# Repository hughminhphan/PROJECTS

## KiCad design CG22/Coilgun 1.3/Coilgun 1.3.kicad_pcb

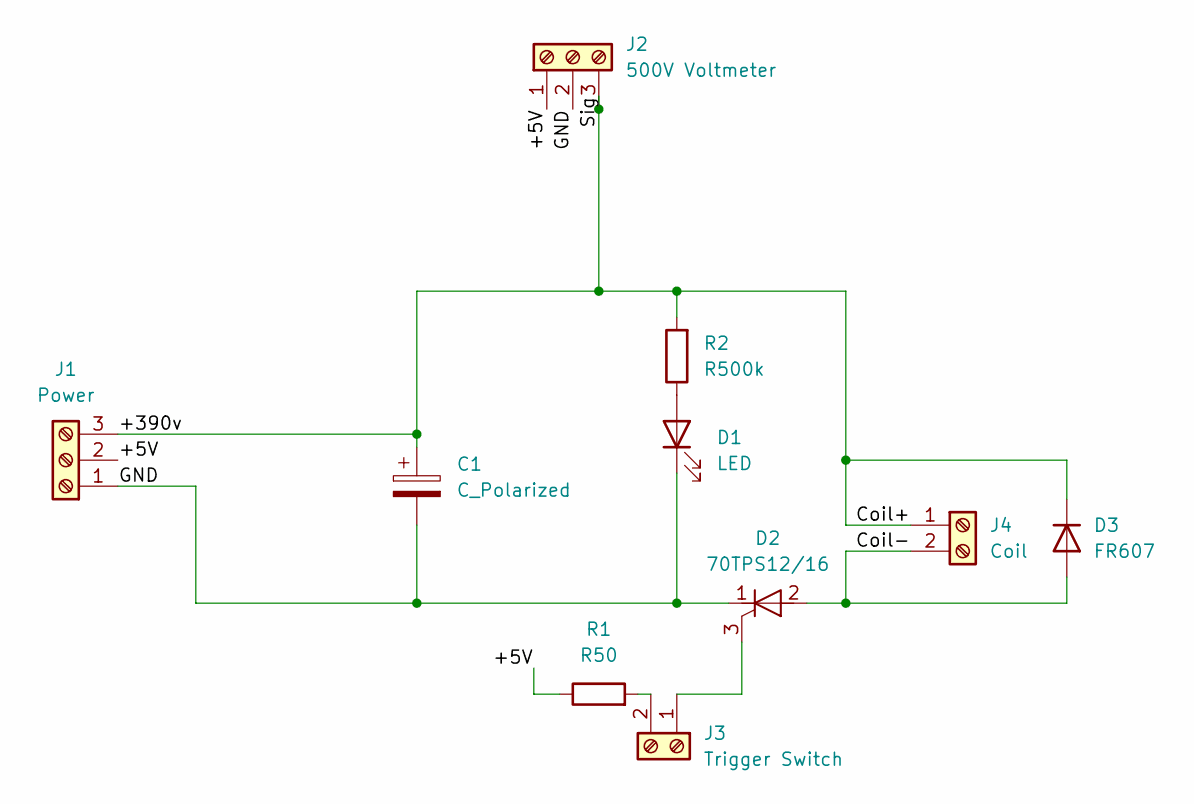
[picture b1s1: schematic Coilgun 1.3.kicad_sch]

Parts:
C1: C_Polarized
D1: LED; LED_D5.0mm
D2: 70TPS12/16; TO-247-3_Vertical
D3: FR607; D_DO-27_P15.24mm_Horizontal
J1: Power; TerminalBlock_bornier-3_P5.08mm
J2: 500V Voltmeter; TerminalBlock_bornier-3_P5.08mm
J3: Trigger Switch; TerminalBlock_bornier-2_P5.08mm
J4: Coil; TerminalBlock_bornier-2_P5.08mm
R1: R50; R_Axial_DIN0309_L9.0mm_D3.2mm_P12.70mm_Horizontal
R2: R500k; R_Axial_DIN0309_L9.0mm_D3.2mm_P12.70mm_Horizontal

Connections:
/+5V: J1.2, J2.1, R1.1
/+390v: C1.1, D3.1 (K), J1.3, J2.3, J4.1, R2.2
/Coil-: D2.2 (A), D3.2 (A), J4.2
/GND: C1.2, D1.1 (K), D2.1 (K), J1.1, J2.2
unnamed: D1.2 (A), R2.1
unnamed: D2.3 (G), J3.1
unnamed: J3.2, R1.2

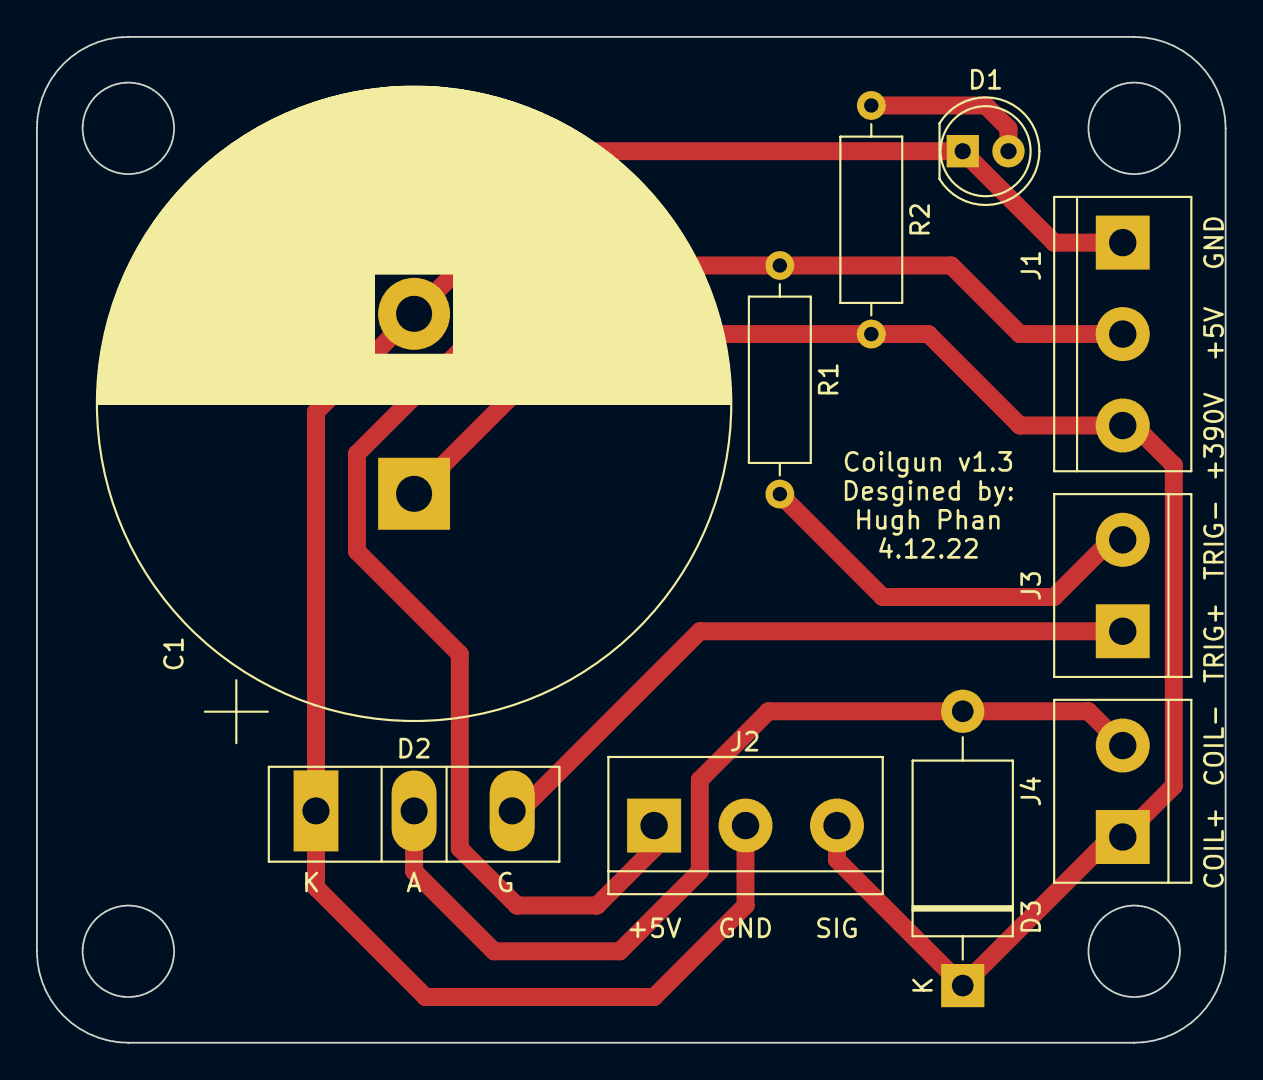
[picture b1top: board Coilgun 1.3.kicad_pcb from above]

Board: 2 copper layers, 66.0 x 55.9 mm, 10 parts (0 on the bottom side), 7 nets.

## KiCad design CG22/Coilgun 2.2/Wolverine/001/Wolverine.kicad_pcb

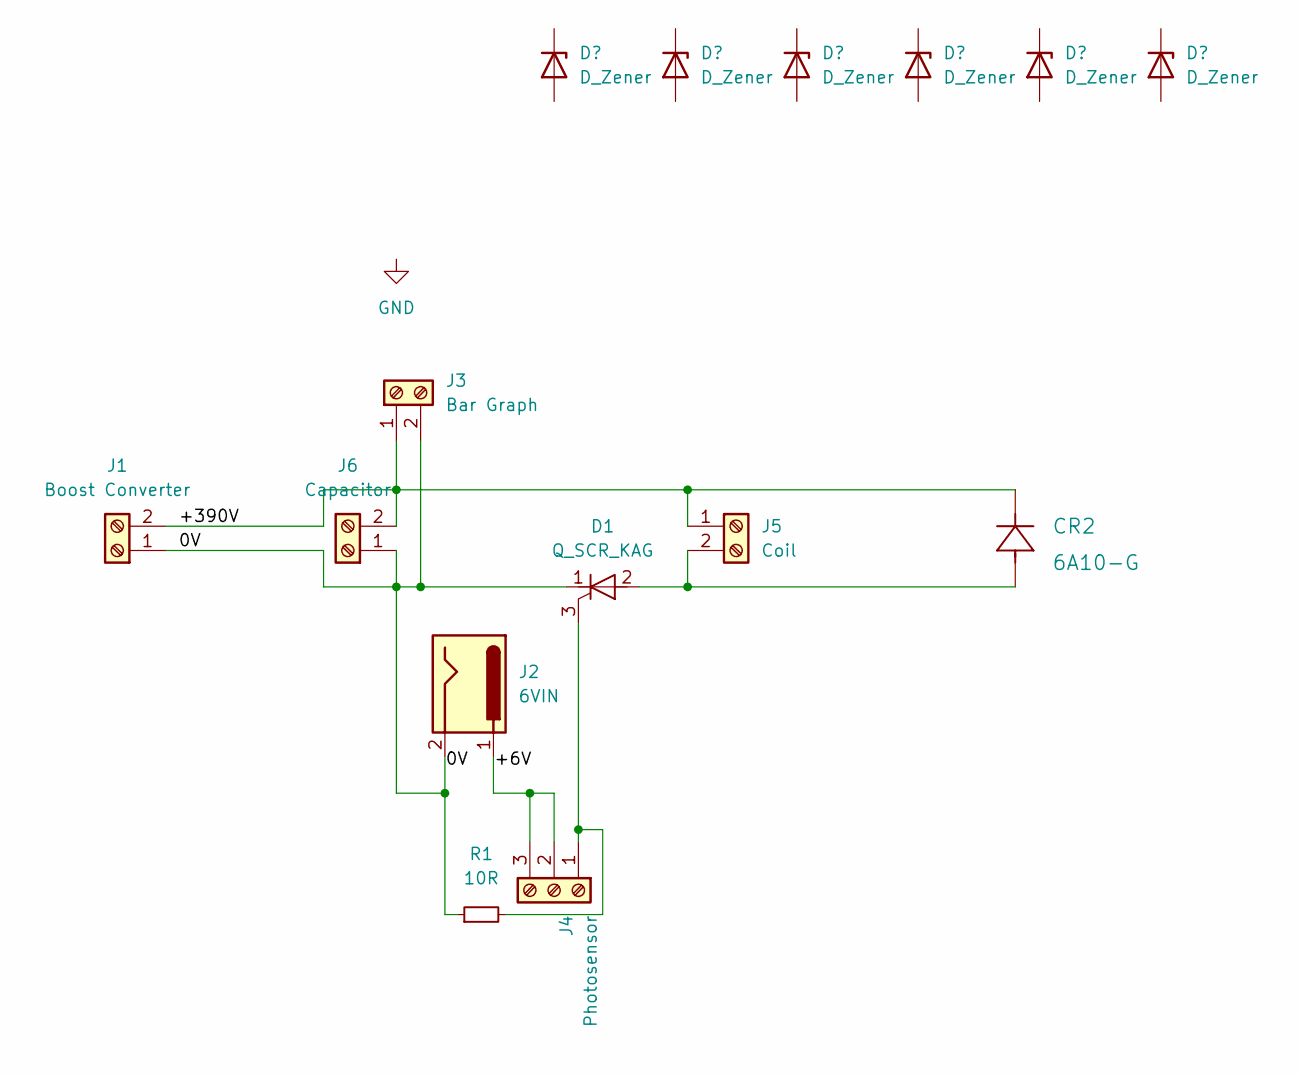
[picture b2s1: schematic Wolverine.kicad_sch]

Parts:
CR2: 6A10-G; D_P600_R-6_P20.00mm_Horizontal
D1: Q_SCR_KAG; TO-247-3_Horizontal_TabDown
J1: Boost Converter; TerminalBlock_Altech_AK300-2_P5.00mm
J2: 6VIN; BarrelJack_Horizontal
J3: Bar Graph; TerminalBlock_Altech_AK300-2_P5.00mm
J4: Photosensor; TerminalBlock_Altech_AK300-3_P5.00mm
J5: Coil; TerminalBlock_Altech_AK300-2_P5.00mm
J6: Capacitor; TerminalBlock_Altech_AK300-2_P5.00mm
R1: 10R; R_Axial_DIN0207_L6.3mm_D2.5mm_P10.16mm_Horizontal

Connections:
/0V: D1.1 (K), J1.1, J2.2, J3.2, J6.1, R1.1
/+6V: J2.1, J4.2, J4.3
/+390V: CR2.1, J1.2, J3.1, J5.1, J6.2
unnamed: CR2.2, D1.2 (A), J5.2
unnamed: D1.3 (G), J4.1, R1.2

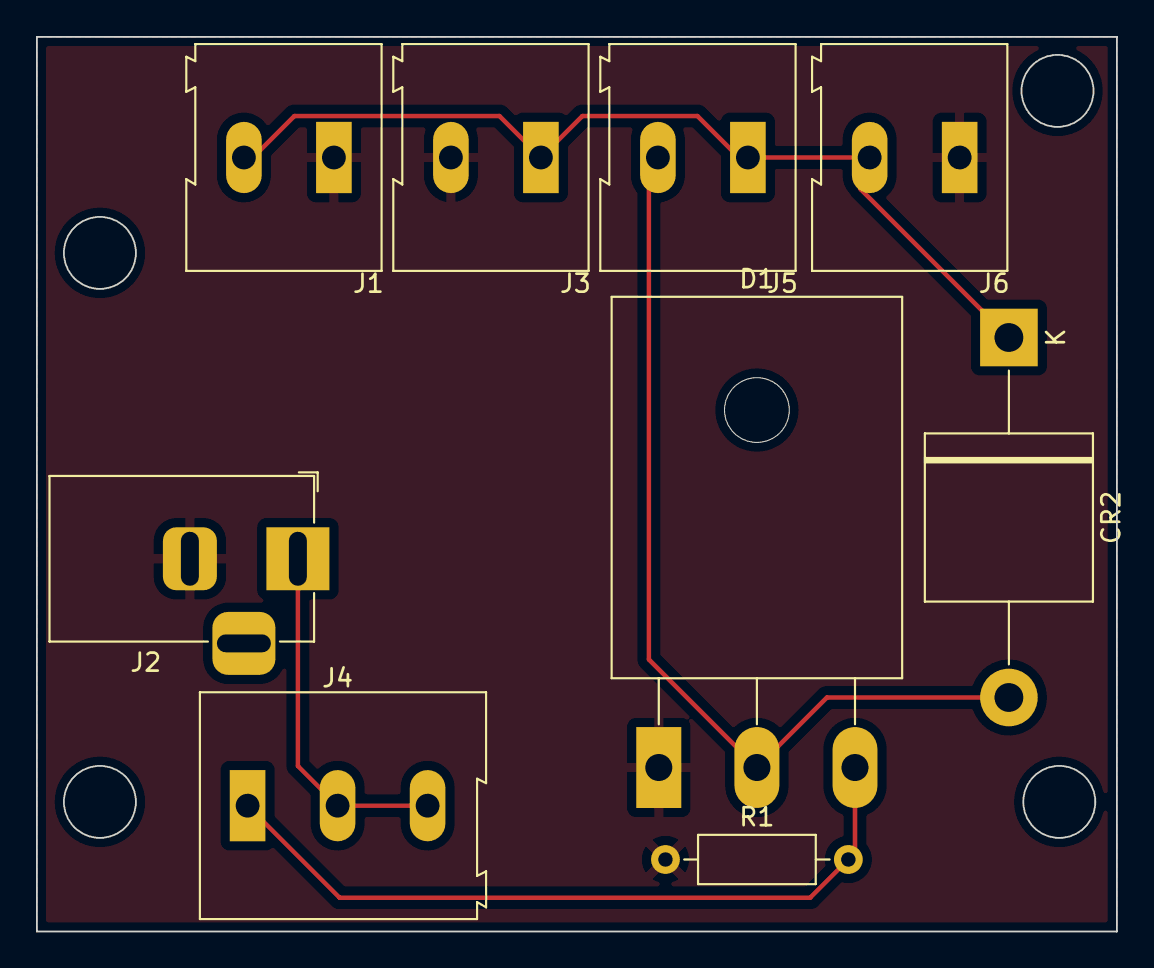
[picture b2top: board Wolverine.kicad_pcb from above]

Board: 2 copper layers, 60.0 x 49.7 mm, 9 parts (0 on the bottom side), 5 nets.

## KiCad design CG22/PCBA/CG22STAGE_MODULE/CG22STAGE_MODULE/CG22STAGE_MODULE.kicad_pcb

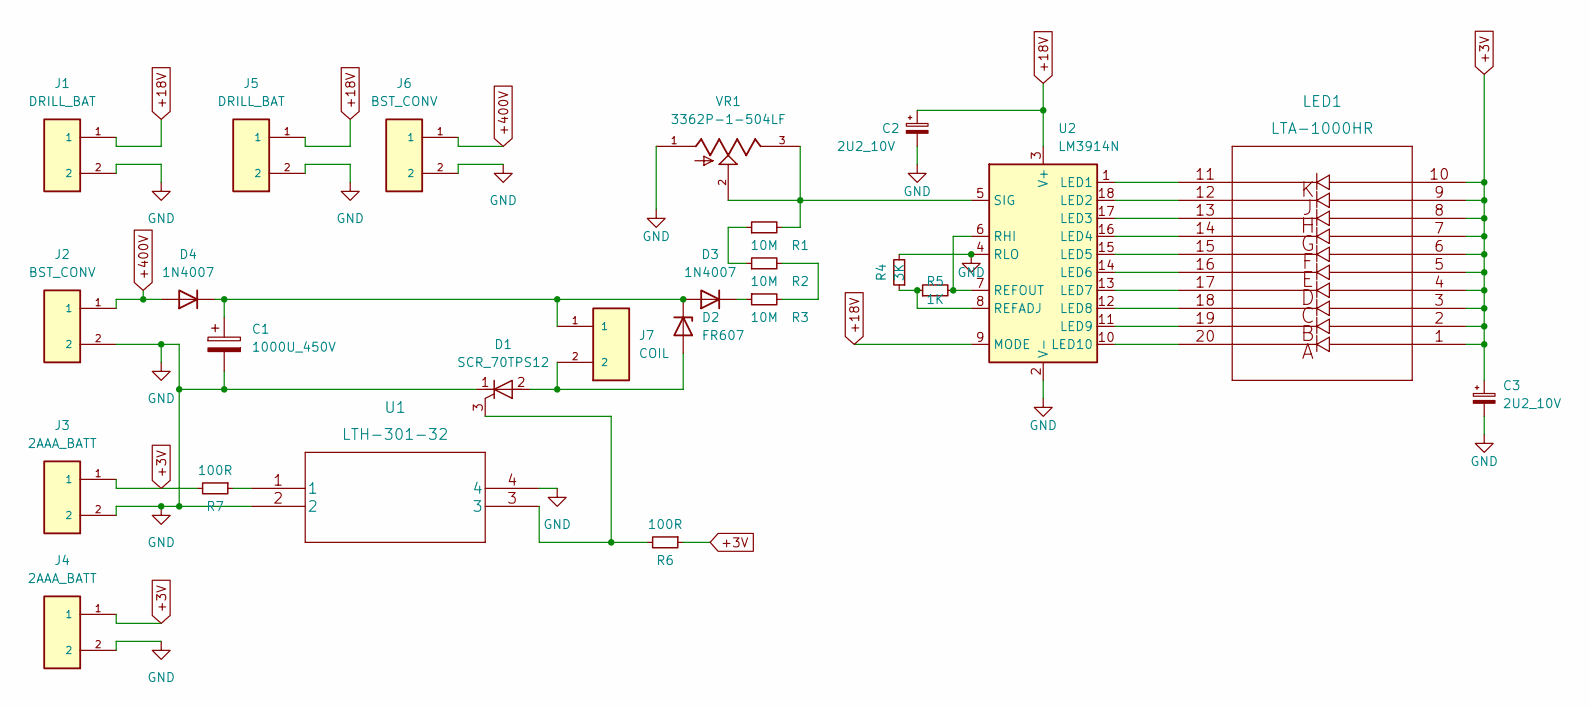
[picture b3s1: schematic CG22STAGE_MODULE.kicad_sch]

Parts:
C1: 1000U_450V; CP_Radial_D35.0mm_P10.00mm_SnapIn
C2, C3: 2U2_10V; CP_Radial_D4.0mm_P2.00mm
D1: SCR_70TPS12; TO-247-3_Vertical
D2: FR607; D_P600_R-6_P12.70mm_Horizontal
D3, D4: 1N4007; D_DO-41_SOD81_P10.16mm_Horizontal
J1, J5: DRILL_BAT; 2 Position Wire to Board Terminal Block Horizontal with Boa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
J2, J6: BST_CONV; 2 Position Wire to Board Terminal Block Horizontal with Boa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
J3, J4: 2AAA_BATT; 2 Position Wire to Board Terminal Block Horizontal with Boa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
J7: COIL; 2 Position Wire to Board Terminal Block Horizontal with Boa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
LED1: LTA-1000HR
R1, R2, R3: 10M; R_Axial_DIN0204_L3.6mm_D1.6mm_P7.62mm_Horizontal
R4: 3K; R_Axial_DIN0204_L3.6mm_D1.6mm_P7.62mm_Horizontal
R5: 1K; R_Axial_DIN0204_L3.6mm_D1.6mm_P7.62mm_Horizontal
R6, R7: 100R; R_Axial_DIN0204_L3.6mm_D1.6mm_P7.62mm_Horizontal
U1: LTH-301-32
U2: LM3914N; DIP-18_W7.62mm_LongPads
VR1: 3362P-1-504LF; PARTREV 08/26/10

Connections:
+3V: C3.1, J3.1, J4.1, LED1.1, LED1.2, LED1.3, LED1.4, LED1.5, LED1.6, LED1.7, LED1.8, LED1.9, LED1.10, R6.1, R7.2
+18V: C2.1, J1.1, J5.1, U2.3 (V+), U2.9 (MODE)
+400V: D4.2 (A), J2.1, J6.1
GND: C1.2, C2.2, C3.2, D1.1 (K), J1.2, J2.2, J3.2, J4.2, J5.2, J6.2, R4.2, U1.2, U1.4, U2.2 (V-), U2.4 (RLO), VR1.1
unnamed: C1.1, D2.1 (A1), D3.2 (A), D4.1 (K), J7.1
unnamed: D1.2 (A), D2.2 (A2), J7.2
unnamed: D1.3 (G), R6.2, U1.3
unnamed: D3.1 (K), R3.1
unnamed: LED1.11, U2.1 (LED1)
unnamed: LED1.12, U2.18 (LED2)
unnamed: LED1.13, U2.17 (LED3)
unnamed: LED1.14, U2.16 (LED4)
unnamed: LED1.15, U2.15 (LED5)
unnamed: LED1.16, U2.14 (LED6)
unnamed: LED1.17, U2.13 (LED7)
unnamed: LED1.18, U2.12 (LED8)
unnamed: LED1.19, U2.11 (LED9)
unnamed: LED1.20, U2.10 (LED10)
unnamed: R1.1, R2.1
unnamed: R1.2, U2.5 (SIG), VR1.2, VR1.3
unnamed: R2.2, R3.2
unnamed: R4.1, R5.1, U2.8 (REFADJ)
unnamed: R5.2, U2.6 (RHI), U2.7 (REFOUT)
unnamed: R7.1, U1.1

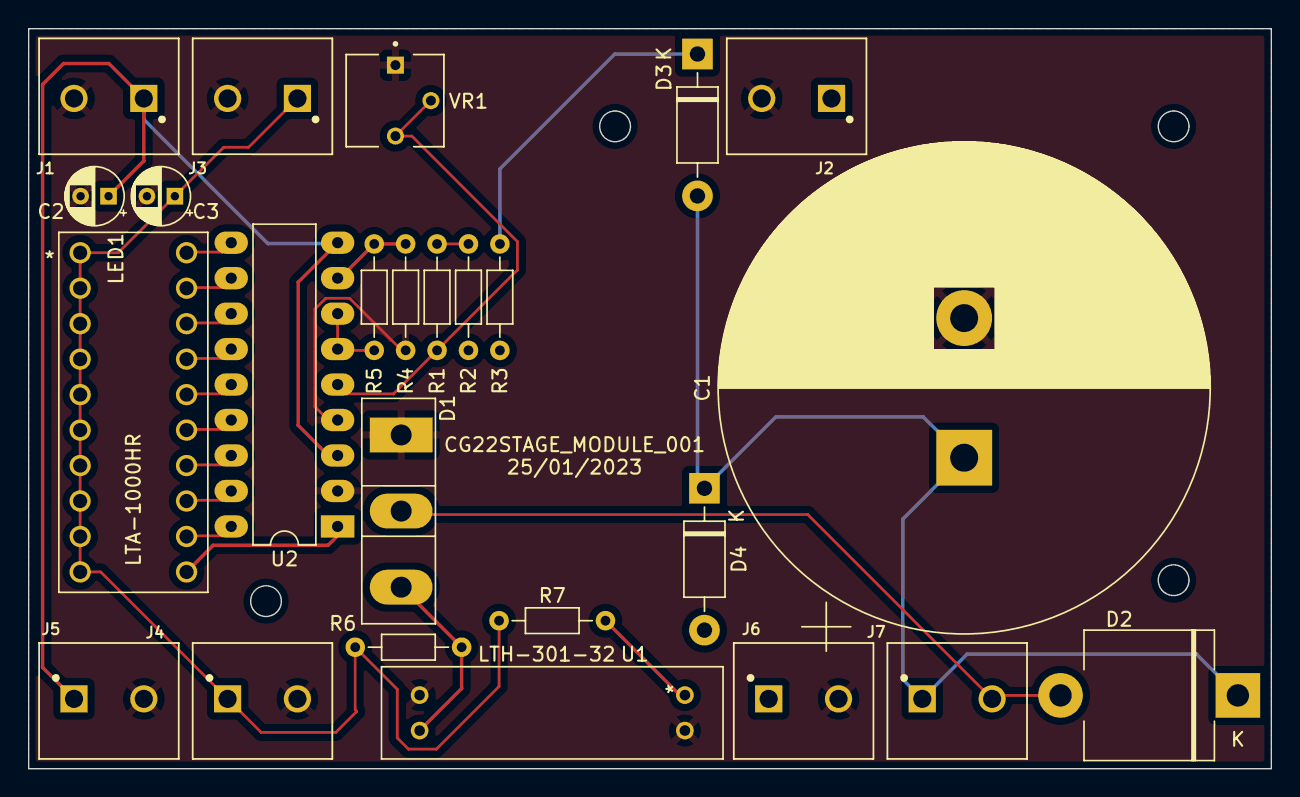
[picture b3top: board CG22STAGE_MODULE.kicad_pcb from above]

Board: 2 copper layers, 89.0 x 53.0 mm, 25 parts (0 on the bottom side), 24 nets.

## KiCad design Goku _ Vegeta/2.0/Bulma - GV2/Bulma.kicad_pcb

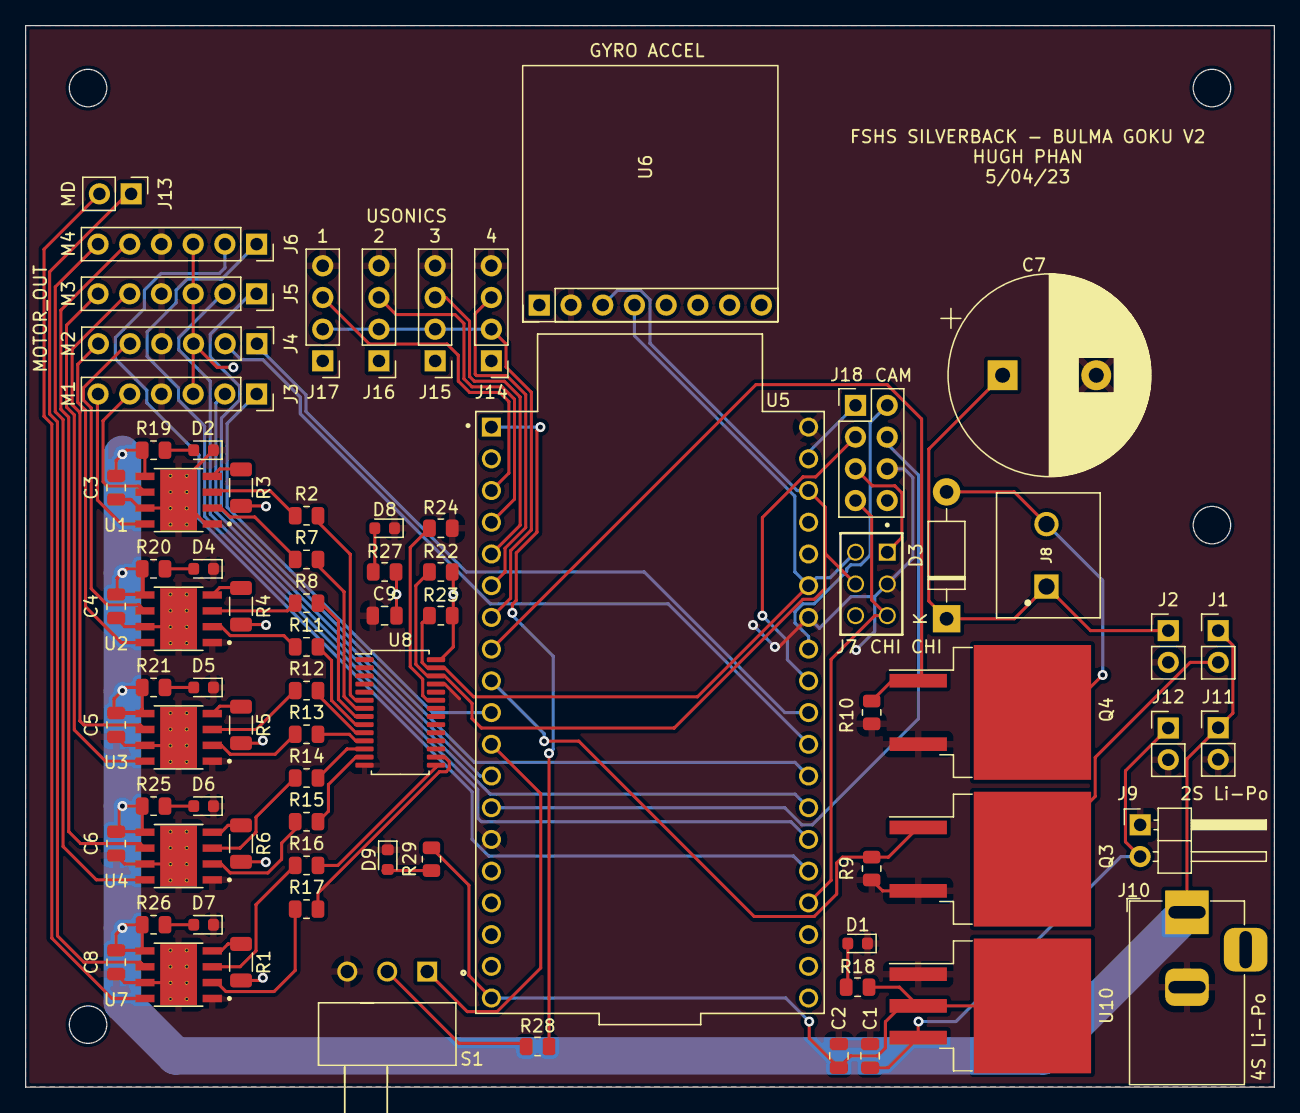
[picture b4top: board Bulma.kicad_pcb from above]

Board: 2 copper layers, 100.0 x 85.0 mm, 77 parts (0 on the bottom side), 76 nets.

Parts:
C1, C2: 10UF20V; C_0805_2012Metric
C3, C4, C5, C6, C8: 0.1UF20V; C_0805_2012Metric
C7: 1000U; CP_Radial_D16.0mm_P7.50mm
C9: 10UF; C_0805_2012Metric
D1, D2, D4, D5, D6, D7, D8, D9: LED; LED_0603_1608Metric
D3: 1N4004; D_DO-41_SOD81_P10.16mm_Horizontal
J1: BOOST CONVERTER IN; PinHeader_1x02_P2.54mm_Vertical
J2: BOOST CONVERTER OUT; PinHeader_1x02_P2.54mm_Vertical
J3: Drive Motor 1; PinSocket_1x06_P2.54mm_Vertical
J4: Drive Motor 2; PinHeader_1x06_P2.54mm_Vertical
J5: Drive Motor 3; PinSocket_1x06_P2.54mm_Vertical
J6: Drive Motor 4; PinSocket_1x06_P2.54mm_Vertical
J7: Chi Chi Conn; SAMTEC_SSQ-103-01-T-D
J8: Solenoid; 2 Position Wire to Board Terminal Block Horizontal with Boa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
J9: 2S Li-Po; PinHeader_1x02_P2.54mm_Horizontal
J10: 4S Li-Po; BarrelJack_Horizontal
J11: Voltmeter 1; PinHeader_1x02_P2.54mm_Vertical
J12: Voltmeter 2; PinHeader_1x02_P2.54mm_Vertical
J13: Dribbler Motor 1; PinHeader_1x02_P2.54mm_Vertical
J14: USONIC1; PinHeader_1x04_P2.54mm_Vertical
J15: USONIC2; PinHeader_1x04_P2.54mm_Vertical
J16: USONIC3; PinHeader_1x04_P2.54mm_Vertical
J17: USONIC4; PinHeader_1x04_P2.54mm_Vertical
J18: Cam H7; PinHeader_2x04_P2.54mm_Vertical
Q3, Q4: IRLZ44N; TO-263-2
R1, R3, R4, R5, R6: 200R; R_1206_3216Metric
R2, R7, R8, R11, R12, R13, R14, R15, R16, R17, R28: 220R; R_0805_2012Metric
R9, R10, R22, R23, R24: 10K; R_0805_2012Metric
R18, R27, R29: 150R; R_0805_2012Metric
R19, R20, R21, R25, R26: 730R; R_0805_2012Metric
S1: 1825116-1; SW_1825116-1
U1, U2, U3, U4, U7: DRV8870DDAR; VREG_LM5017MR_NOPB
U5: ESP32-DEVKITC; MODULE_ESP32-DEVKITC
U6: GY-521
U8: PCA9685PW; TSSOP-28_4.4x9.7mm_P0.65mm
U10: LM1084-5.0; TO-263-3_TabPin2

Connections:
+3.3V: R28.2, U5.1 (3V3)
+5V: C2.1, C9.1, J3.3, J4.3, J5.3, J6.3, J7.01, J14.1, J15.1, J16.1, J17.1, J18.5, R1.2, R3.2, R4.2, R5.2, R6.2, R18.2, R22.2, R23.2, R27.2, R29.2, U5.19 (EXT_5V), U6.1 (VCC), U8.28 (VDD), U10.2 (VO)
+7.5V: C1.1, J9.2, J12.1, U10.3 (VI)
+15V: C3.1, C4.1, C5.1, C6.1, C8.1, J1.1, J10.1, J11.1, R19.2, R20.2, R21.2, R25.2, R26.2, U1.5 (VM), U2.5 (VM), U3.5 (VM), U4.5 (VM), U7.5 (VM)
+48V: C7.1, D3.1 (K), J2.1, J8.1
/CAM SS: J18.4, U5.13 (IO12)
/CHRGEN: Q3.1 (G), R9.1, U5.9 (IO25)
/KCKEN: Q4.1 (G), R10.1, U5.8 (IO33)
/M1ENCA: J3.2, U5.12 (IO14)
/M1ENCB: J3.1, U5.10 (IO26)
/M2ENCA: J4.2, U5.28 (IO17)
/M2ENCB: J4.1, U5.29 (IO5)
/M3ENCA: J5.2, U5.26 (IO4)
/M3ENCB: J5.1, U5.27 (IO16)
/M4ENCA: J6.2, U5.24 (IO2)
/M4ENCB: J6.1, U5.25 (IO0)
/MISO: J18.2, U5.31 (IO19)
/MOSI: J18.1, U5.37 (IO23)
/RST: J7.05, J18.7, U5.23 (IO15)
/SCK: J18.3, U5.30 (IO18)
/SCL: J7.04, R22.1, U5.36 (IO22), U6.3 (SCL), U8.26 (SCL)
/SDA: J7.02, R23.1, U5.33 (IO21), U6.4 (SDA), U8.27 (SDA)
/SW1: S1.1, U5.11 (IO27)
/UECHO1: J14.3, U5.6 (IO35)
/UECHO2: J15.3, U5.5 (IO34)
/UECHO3: J16.3, U5.4 (SENSOR_VN)
/UECHO4: J17.3, U5.3 (SENSOR_VP)
/UTRIG: J14.2, J15.2, J16.2, J17.2, U5.7 (IO32)
GND: C1.2, C2.2, C3.2, C4.2, C5.2, C6.2, C7.2, C8.2, C9.2, D1.1 (K), D2.1 (K), D4.1 (K), D5.1 (K), D6.1 (K), D7.1 (K), D8.1 (K), D9.1 (K), J2.2, J3.4, J4.4, J5.4, J6.4, J7.03, J9.1, J10.2, J11.2, J12.2, J14.4, J15.4, J16.4, J17.4, J18.6, Q3.3 (S), Q4.3 (S), R9.2, R10.2, R24.2, S1.3, U1.1 (GND), U1.7 (ISEN), U1.9 (PAD), U2.1 (GND), U2.7 (ISEN), U2.9 (PAD), U3.1 (GND), U3.7 (ISEN), U3.9 (PAD), U4.1 (GND), U4.7 (ISEN), U4.9 (PAD), U5.14 (GND1), U5.32 (GND2), U5.38 (GND3), U6.2 (GND), U7.1 (GND), U7.7 (ISEN), U7.9 (PAD), U8.14 (VSS), U8.25 (EXTCLK), U10.1 (GND)
unnamed: D1.2 (A), R18.1
unnamed: D2.2 (A), R19.1
unnamed: D3.2 (A), J8.2, Q4.2 (D)
unnamed: D4.2 (A), R20.1
unnamed: D5.2 (A), R21.1
unnamed: D6.2 (A), R25.1
unnamed: D7.2 (A), R26.1
unnamed: D8.2 (A), R27.1
unnamed: D9.2 (A), R29.1
unnamed: J1.2, Q3.2 (D)
unnamed: J3.5, U1.6 (OUT1)
unnamed: J3.6, U1.8 (OUT2)
unnamed: J4.5, U2.6 (OUT1)
unnamed: J4.6, U2.8 (OUT2)
unnamed: J5.5, U3.6 (OUT1)
unnamed: J5.6, U3.8 (OUT2)
unnamed: J6.5, U4.6 (OUT1)
unnamed: J6.6, U4.8 (OUT2)
unnamed: J13.1, U7.6 (OUT1)
unnamed: J13.2, U7.8 (OUT2)
unnamed: R1.1, U7.4 (VREF)
unnamed: R2.1, U1.3 (IN1)
unnamed: R2.2, U8.6 (LED0)
unnamed: R3.1, U1.4 (VREF)
unnamed: R4.1, U2.4 (VREF)
unnamed: R5.1, U3.4 (VREF)
unnamed: R6.1, U4.4 (VREF)
unnamed: R7.1, U1.2 (IN2)
unnamed: R7.2, U8.7 (LED1)
unnamed: R8.1, U2.3 (IN1)
unnamed: R8.2, U8.8 (LED2)
unnamed: R11.1, U2.2 (IN2)
unnamed: R11.2, U8.9 (LED3)
unnamed: R12.1, U3.3 (IN1)
unnamed: R12.2, U8.10 (LED4)
unnamed: R13.1, U3.2 (IN2)
unnamed: R13.2, U8.11 (LED5)
unnamed: R14.1, U4.3 (IN1)
unnamed: R14.2, U8.12 (LED6)
unnamed: R15.1, U4.2 (IN2)
unnamed: R15.2, U8.13 (LED7)
unnamed: R16.1, U7.3 (IN1)
unnamed: R16.2, U8.15 (LED8)
unnamed: R17.1, U7.2 (IN2)
unnamed: R17.2, U8.16 (LED9)
unnamed: R24.1, U8.23 (~OE)
unnamed: R28.1, S1.2

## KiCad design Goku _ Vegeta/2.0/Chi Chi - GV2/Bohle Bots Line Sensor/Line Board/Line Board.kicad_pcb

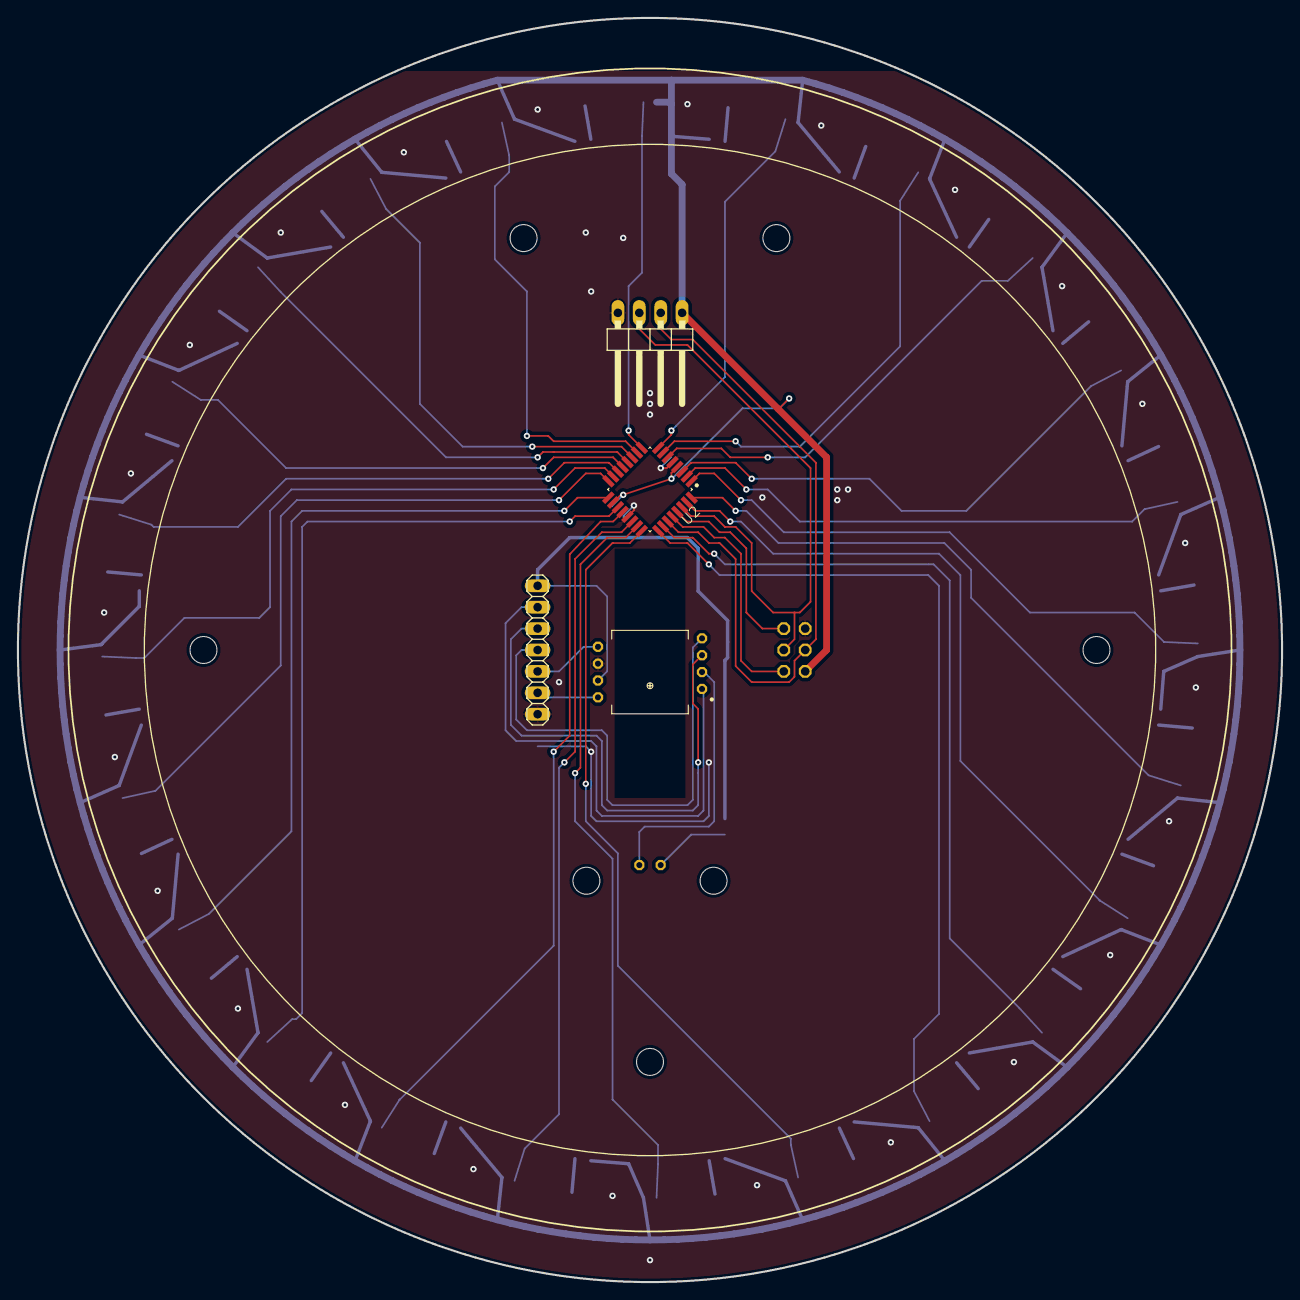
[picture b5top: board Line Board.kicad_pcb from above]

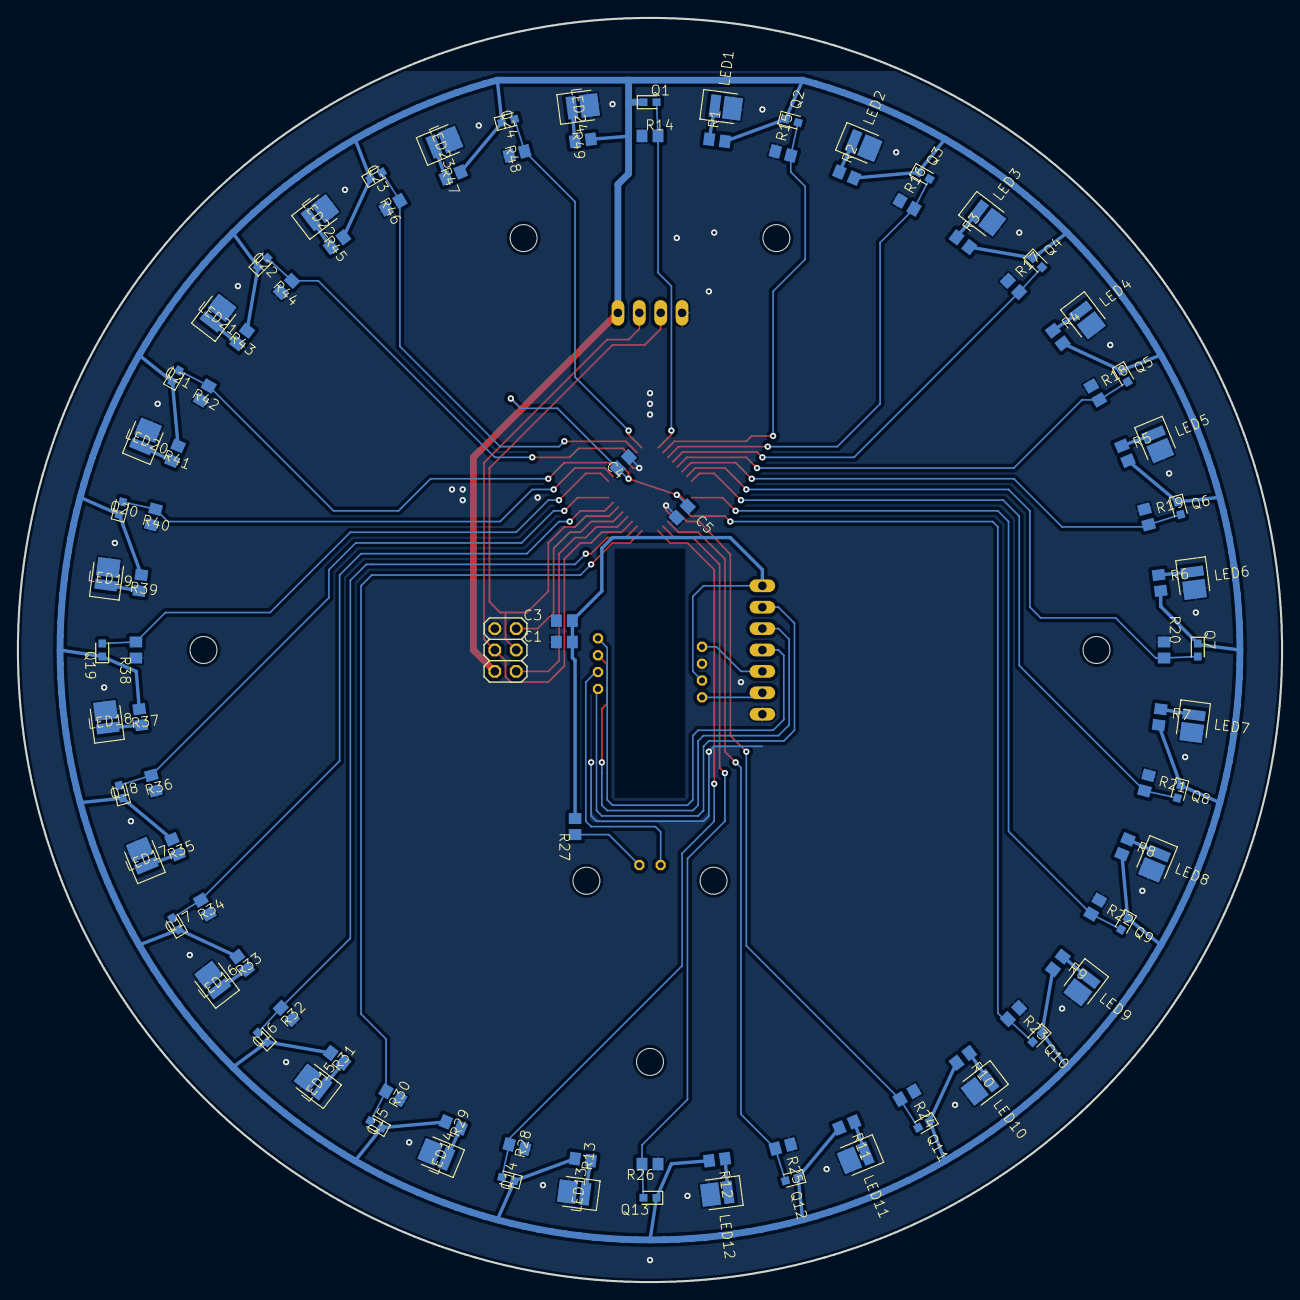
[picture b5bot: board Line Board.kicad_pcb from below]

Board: 2 copper layers, 150.0 x 150.0 mm, 112 parts (102 on the bottom side), 62 nets.

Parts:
@HOLE0, @HOLE1, @HOLE2, @HOLE3, @HOLE4: (no value)
C1, C4, C5: 0.1uF; C0805
C3: 1uF; C0805
JP1: 2X03
JP2: 1X04_90
JP4: 1X07
LED1, LED2, LED3, LED4, LED5, LED6, LED7, LED8, LED9, LED10, LED11, LED12, LED13, LED14, LED15, LED16, LED17, LED18, LED19, LED20, LED21, LED22, LED23, LED24: STW8A12D_LED; LEDC3428X70
Q1, Q2, Q3, Q4, Q5, Q6, Q7, Q8, Q9, Q10, Q11, Q12, Q13, Q14, Q15, Q16, Q17, Q18, Q19, Q20, Q21, Q22, Q23, Q24: ALS-PT19-315C/L177/TR8; LEDC1708X60
R1, R2, R3, R4, R5, R6, R7, R8, R9, R10, R11, R12, R13, R29, R31, R33, R35, R37, R39, R41, R43, R45, R47, R49: 390R; R0805
R14, R15, R16, R17, R18, R19, R20, R21, R22, R23, R24, R25, R26, R28, R30, R32, R34, R36, R38, R40, R42, R44, R46, R48: 10k; R0805
R27: 33R; R0805
U2: ATTINY828; QFP80P900X900X120-32
U3: ADNS3050
U$1: COLORBOARDCUTOUT

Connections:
+3V3: C1.1, C3.1, JP4.1, R27.2, U3.7
+5V: C4.1, C5.1, JP1.2, JP2.1, Q1.C, Q2.C, Q3.C, Q4.C, Q5.C, Q6.C, Q7.C, Q8.C, Q9.C, Q10.C, Q11.C, Q12.C, Q13.C, Q14.C, Q15.C, Q16.C, Q17.C, Q18.C, Q19.C, Q20.C, Q21.C, Q22.C, Q23.C, Q24.C, R1.2, R2.2, R3.2, R4.2, R5.2, R6.2, R7.2, R8.2, R9.2, R10.2, R11.2, R12.2, R13.2, R29.2, R31.2, R33.2, R35.2, R37.2, R39.2, R41.2, R43.2, R45.2, R47.2, R49.2, U2.4, U2.18
COLORSENSOR1: Q1.E, R14.2, U2.9
COLORSENSOR2: Q2.E, R15.2, U2.10
COLORSENSOR3: Q3.E, R16.2, U2.11
COLORSENSOR4: Q4.E, R17.2, U2.12
COLORSENSOR5: Q5.E, R18.2, U2.13
COLORSENSOR6: Q6.E, R19.2, U2.14
COLORSENSOR7: Q7.E, R20.2, U2.15
COLORSENSOR8: Q8.E, R21.2, U2.16
COLORSENSOR9: Q9.E, R22.2, U2.17
COLORSENSOR10: Q10.E, R23.2, U2.19
COLORSENSOR11: Q11.E, R24.2, U2.20
COLORSENSOR12: Q12.E, R25.2, U2.22
COLORSENSOR13: Q13.E, R26.2, U2.23
COLORSENSOR14: Q14.E, R28.2, U2.24
COLORSENSOR15: Q15.E, R30.2, U2.25
COLORSENSOR16: Q16.E, R32.2, U2.26
COLORSENSOR17: Q17.E, R34.2, U2.31
COLORSENSOR18: Q18.E, R36.2, U2.32
COLORSENSOR19: Q19.E, R38.2, U2.1
COLORSENSOR20: Q20.E, R40.2, U2.2
COLORSENSOR21: Q21.E, R42.2, U2.3
COLORSENSOR22: Q22.E, R44.2, U2.6
COLORSENSOR23: Q23.E, R46.2, U2.7
COLORSENSOR24: Q24.E, R48.2, U2.8
GND: C1.2, C3.2, C4.2, C5.2, JP1.6, JP2.4, JP4.7, LED1.2, LED2.2, LED3.2, LED4.2, LED5.2, LED6.2, LED7.2, LED8.2, LED9.2, LED10.2, LED11.2, LED12.2, LED13.2, LED14.2, LED15.2, LED16.2, LED17.2, LED18.2, LED19.2, LED20.2, LED21.2, LED22.2, LED23.2, LED24.2, R14.1, R15.1, R16.1, R17.1, R18.1, R19.1, R20.1, R21.1, R22.1, R23.1, R24.1, R25.1, R26.1, R28.1, R30.1, R32.1, R34.1, R36.1, R38.1, R40.1, R42.1, R44.1, R46.1, R48.1, U2.5, U2.21, U3.6
MISO: JP1.1, U2.28
MOSI/SDA: JP1.4, JP2.2, U2.27
MOUSECS: JP4.4, U3.4
MOUSEMISO: JP4.2, U3.1
MOUSEMOSI: JP4.3, U3.3
MOUSEMOTION: JP4.6, U3.8
MOUSESCK: JP4.5, U3.5
unnamed: LED1.1, R1.1
unnamed: U3.2, U3.K
unnamed: R27.1, U3.A
unnamed: LED2.1, R2.1
unnamed: LED3.1, R3.1
unnamed: LED4.1, R4.1
unnamed: LED5.1, R5.1
unnamed: LED6.1, R6.1
unnamed: LED7.1, R7.1
unnamed: LED8.1, R8.1
unnamed: LED9.1, R9.1
unnamed: LED10.1, R10.1
unnamed: LED11.1, R11.1
unnamed: LED12.1, R12.1
unnamed: LED13.1, R13.1
unnamed: LED14.1, R29.1
unnamed: LED15.1, R31.1
unnamed: LED16.1, R33.1
unnamed: LED17.1, R35.1
unnamed: LED18.1, R37.1
unnamed: LED19.1, R39.1
unnamed: LED20.1, R41.1
unnamed: LED21.1, R43.1
unnamed: LED22.1, R45.1
unnamed: LED23.1, R47.1
unnamed: LED24.1, R49.1
RST: JP1.5, U2.29
SCK/SCL: JP1.3, JP2.3, U2.30

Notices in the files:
parts and their libraries:
Copyright 2021 Accelerated Designs. All rights reserved.
COPYRIGHT: Copyright (C) 2018 Accelerated Designs. All rights reserved
